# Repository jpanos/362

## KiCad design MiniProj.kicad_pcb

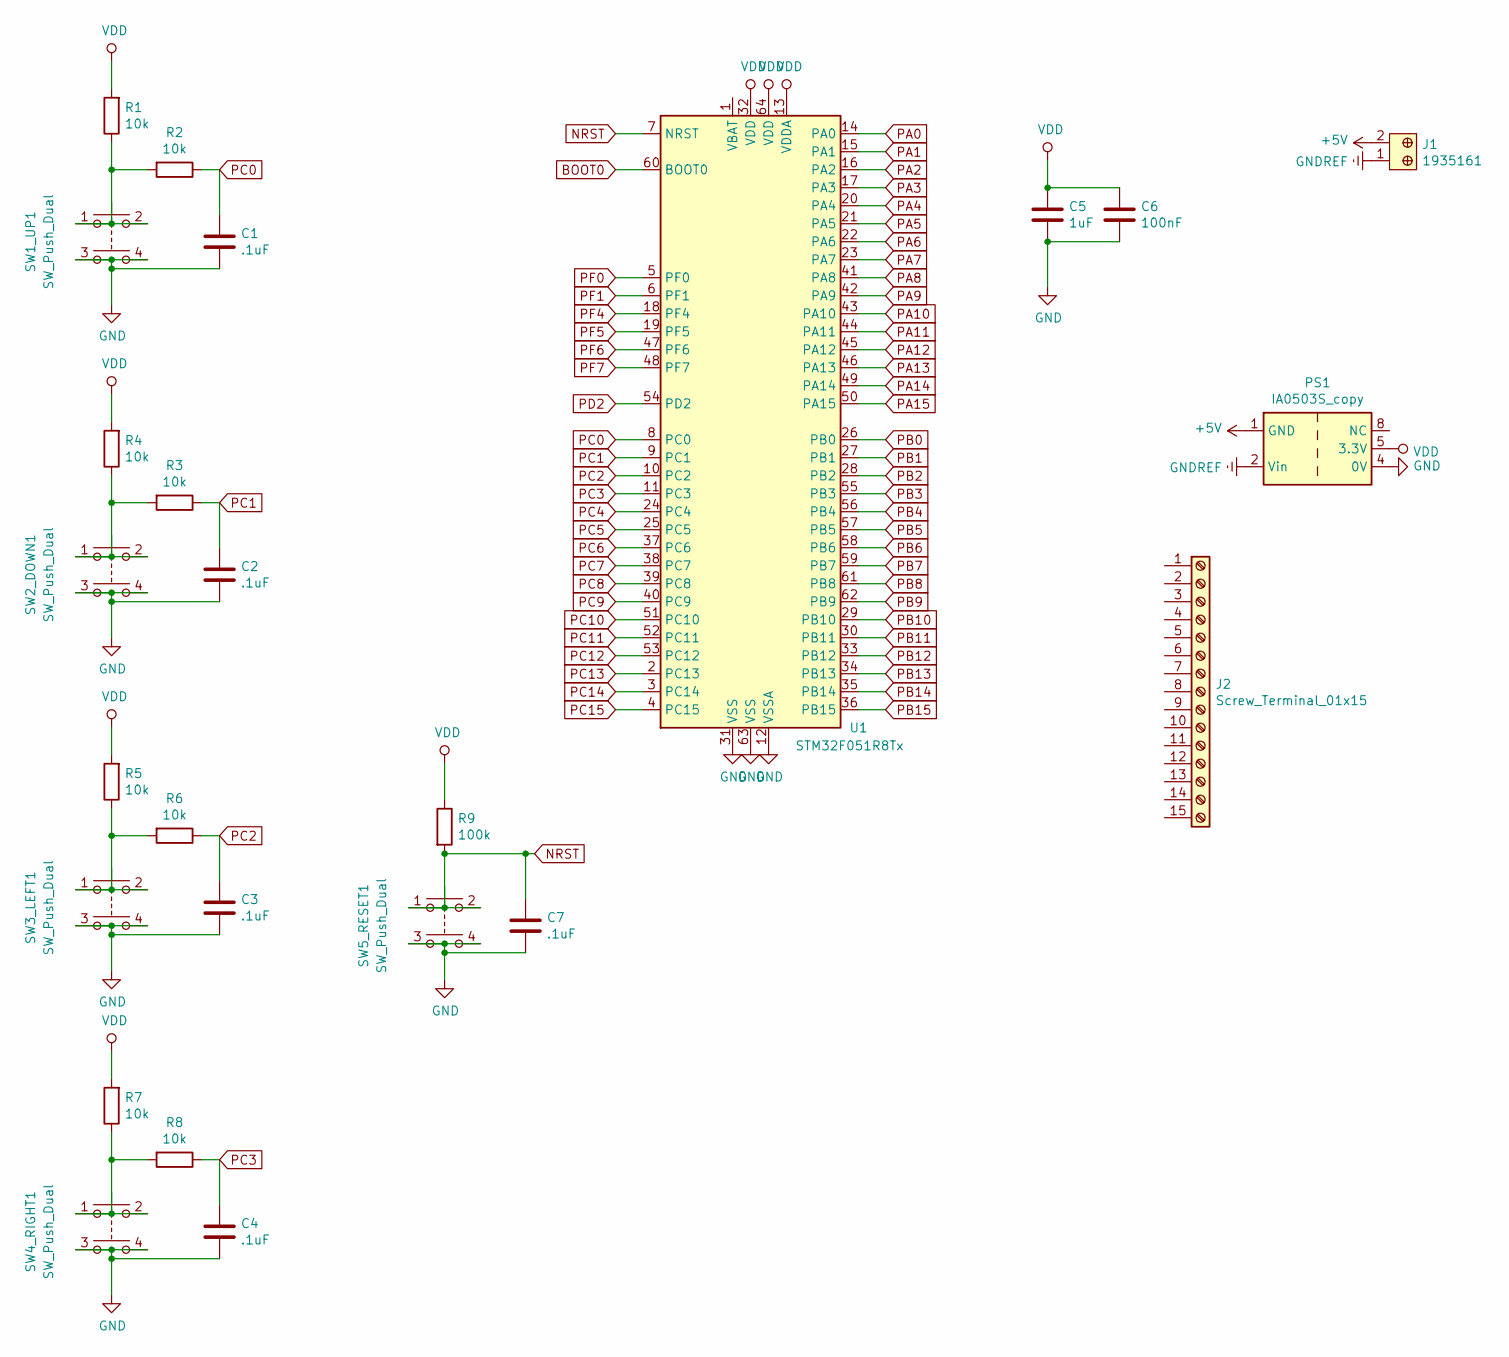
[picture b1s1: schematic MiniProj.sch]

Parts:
C1, C2, C3, C4, C7: .1uF; C_0201_0603Metric
C5: 1uF; C_0402_1005Metric
C6: 100nF; C_0201_0603Metric
J1: 1935161; Terminal_Block_D1.3mm_P5mm; MPN 1935161; Digi-Key_PN 277-1667-ND
J2: Screw_Terminal_01x15; TerminalBlock_4Ucon_1x15_P3.50mm_Horizontal
PS1: IA0503S_copy; CONV_PDS1-S3-S3-M
R1, R2, R3, R4, R5, R6, R7, R8: 10k; R_0402_1005Metric
R9: 100k; R_0402_1005Metric
SW1_UP1, SW2_DOWN1, SW3_LEFT1, SW4_RIGHT1, SW5_RESET1: SW_Push_Dual; SW_TH_Tactile_Omron_B3F-10xx
U1: STM32F051R8Tx; LQFP-64_10x10mm_P0.5mm

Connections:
+5V: J1.2, PS1.1 (GND)
BOOT0: U1.60 (BOOT0)
GND: C1.2, C2.2, C3.2, C4.2, C5.2, C6.2, C7.2, PS1.4 (0V), SW1_UP1.3, SW1_UP1.4, SW2_DOWN1.3, SW2_DOWN1.4, SW3_LEFT1.3, SW3_LEFT1.4, SW4_RIGHT1.3, SW4_RIGHT1.4, SW5_RESET1.3, SW5_RESET1.4, U1.12 (VSSA), U1.31 (VSS), U1.63 (VSS)
GNDREF: J1.1, PS1.2 (Vin)
NRST: C7.1, R9.2, SW5_RESET1.1, SW5_RESET1.2, U1.7 (NRST)
unnamed: R1.1, R2.2, SW1_UP1.1, SW1_UP1.2
unnamed: R3.2, R4.1, SW2_DOWN1.1, SW2_DOWN1.2
unnamed: R5.1, R6.2, SW3_LEFT1.1, SW3_LEFT1.2
unnamed: R7.1, R8.2, SW4_RIGHT1.1, SW4_RIGHT1.2
PA0: U1.14 (PA0)
PA1: U1.15 (PA1)
PA2: U1.16 (PA2)
PA3: U1.17 (PA3)
PA4: U1.20 (PA4)
PA5: U1.21 (PA5)
PA6: U1.22 (PA6)
PA7: U1.23 (PA7)
PA8: U1.41 (PA8)
PA9: U1.42 (PA9)
PA10: U1.43 (PA10)
PA11: U1.44 (PA11)
PA12: U1.45 (PA12)
PA13: U1.46 (PA13)
PA14: U1.49 (PA14)
PA15: U1.50 (PA15)
PB0: U1.26 (PB0)
PB1: U1.27 (PB1)
PB2: U1.28 (PB2)
PB3: U1.55 (PB3)
PB4: U1.56 (PB4)
PB5: U1.57 (PB5)
PB6: U1.58 (PB6)
PB7: U1.59 (PB7)
PB8: U1.61 (PB8)
PB9: U1.62 (PB9)
PB10: U1.29 (PB10)
PB11: U1.30 (PB11)
PB12: U1.33 (PB12)
PB13: U1.34 (PB13)
PB14: U1.35 (PB14)
PB15: U1.36 (PB15)
PC0: C1.1, R2.1, U1.8 (PC0)
PC1: C2.1, R3.1, U1.9 (PC1)
PC2: C3.1, R6.1, U1.10 (PC2)
PC3: C4.1, R8.1, U1.11 (PC3)
PC4: U1.24 (PC4)
PC5: U1.25 (PC5)
PC6: U1.37 (PC6)
PC7: U1.38 (PC7)
PC8: U1.39 (PC8)
PC9: U1.40 (PC9)
PC10: U1.51 (PC10)
PC11: U1.52 (PC11)
PC12: U1.53 (PC12)
PC13: U1.2 (PC13)
PC14: U1.3 (PC14)
PC15: U1.4 (PC15)
PD2: U1.54 (PD2)
PF0: U1.5 (PF0)
PF1: U1.6 (PF1)
PF4: U1.18 (PF4)
PF5: U1.19 (PF5)
PF6: U1.47 (PF6)
PF7: U1.48 (PF7)
VDD: C5.1, C6.1, PS1.5 (3.3V), R1.2, R4.2, R5.2, R7.2, R9.1, U1.13 (VDDA), U1.32 (VDD), U1.64 (VDD)

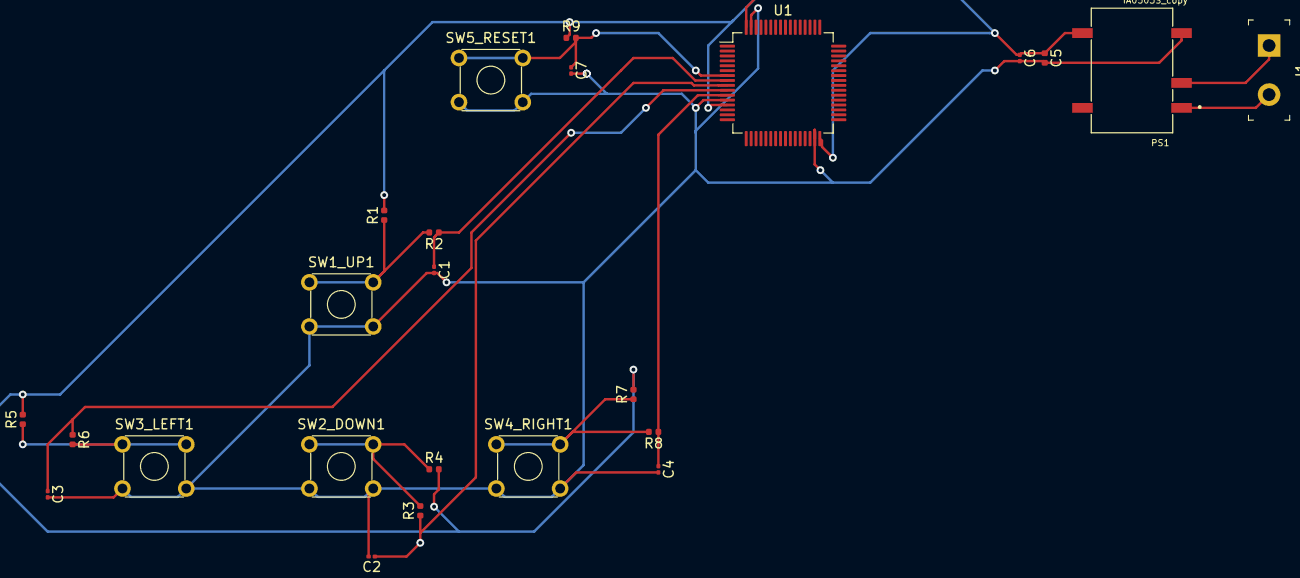
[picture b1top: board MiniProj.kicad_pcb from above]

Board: 2 copper layers, 24 parts (0 on the bottom side), 13 nets.

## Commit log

2019-11-19 df
    df
